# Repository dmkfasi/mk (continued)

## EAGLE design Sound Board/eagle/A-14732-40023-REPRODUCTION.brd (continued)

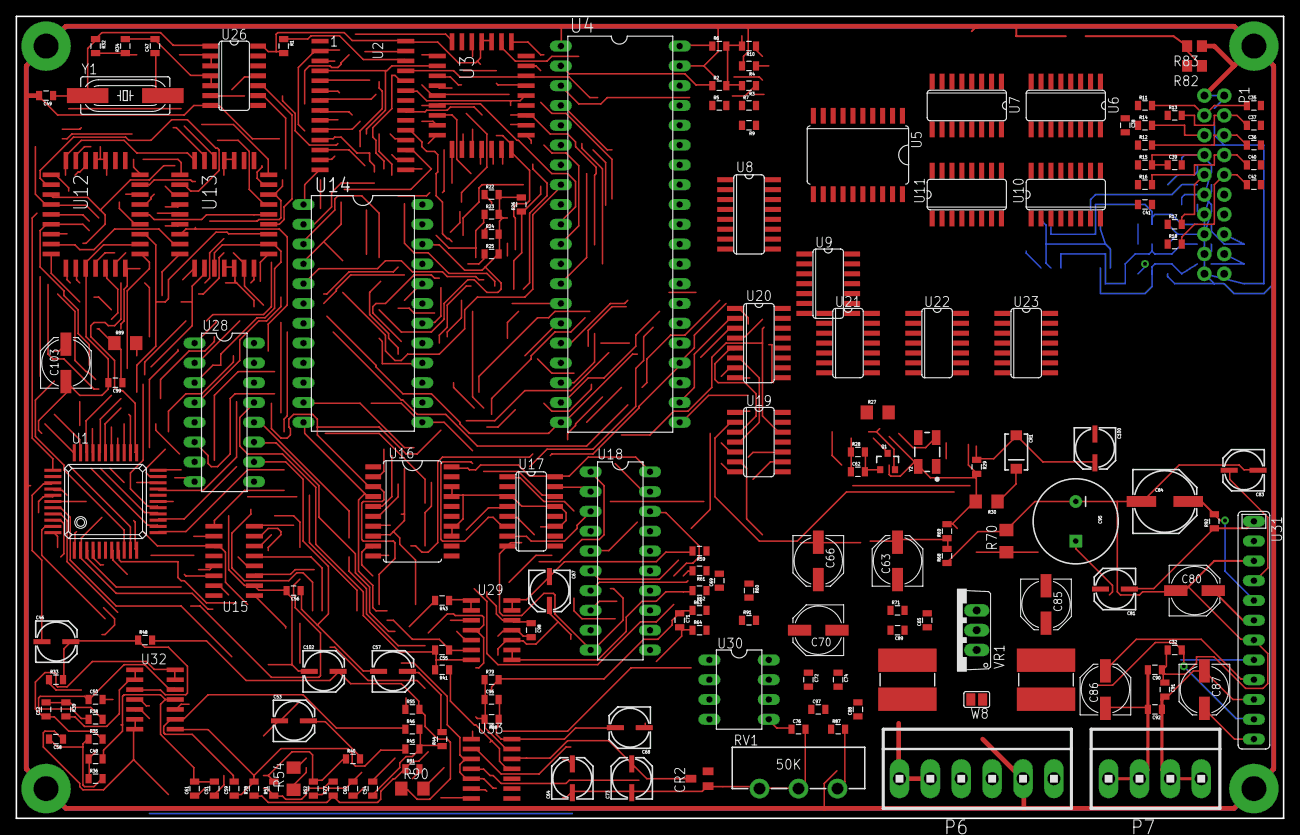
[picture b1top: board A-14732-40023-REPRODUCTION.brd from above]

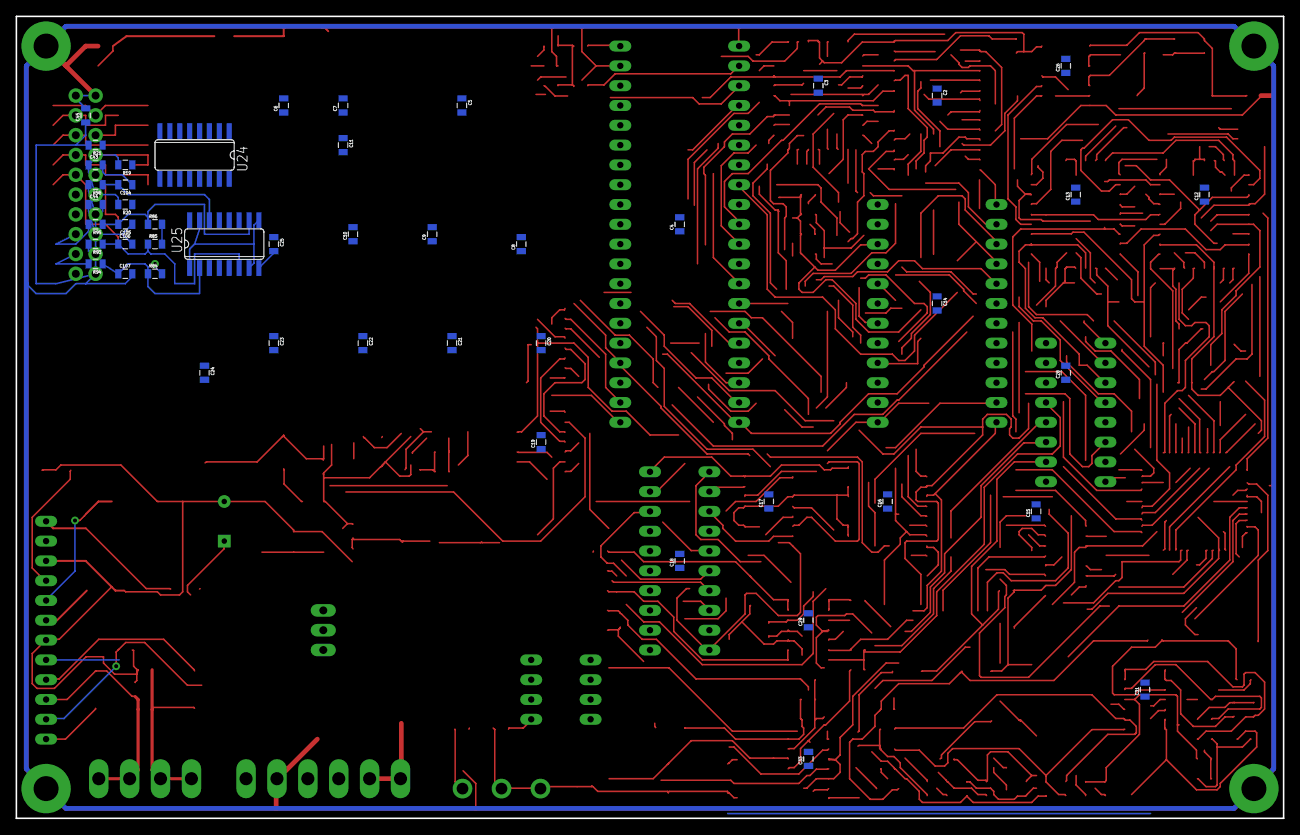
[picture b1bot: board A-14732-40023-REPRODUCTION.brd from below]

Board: 2 copper layers, 162.6 x 102.9 mm, 220 parts (48 on the bottom side), 220 nets.

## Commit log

2015-09-28 4th sheet added
2015-09-28 Removed undo files
2015-09-28 new components added
2015-09-28 fixed packages
2015-10-03 auto regenerated, nothing useful yet
2015-10-05 almost complete 4th sheet
2015-10-05 shortened 26ls31, 26ls32 to fit vertical space
2015-10-06 autogen updated
2015-10-06 P1 connected mostly wired up
2015-10-06 overwritten with new software version
2015-10-09 nothing really new
2015-10-09 completed 4th sheet, some parts name corrected
2015-10-10 regenerated
2015-10-10 26ls32 outputs dir corrected
2015-10-10 fixed YAM-OUT2 net connection, fixed mixed up GND<->AGND, fixed missed power supply pins for U5
2015-10-10 approved non-critical warnings for power supply pins
2015-10-10 approved non-critical power pins warnings
2015-10-10 first revision for 40023 assembly and T-Unit CPU board
2015-10-10 1N5232 SOT-23 package added
2015-10-10 R65 replaced with CR2 according to the official schematics
2015-10-10 1N5232 MiniMELF package added
2015-10-10 updated values, names, fixed some parts, added C104-C107 and R94-R96
2015-10-10 current version
2015-10-11 small fixes, WIP
2015-10-11 added polarized capacitors for PANASONIC_C package
2015-10-11 replaced all non-power rail resistors to 0805 size 1/8W
2015-10-11 replaced filter capacitors to 0805 size
2015-10-11 current project
2015-10-11 replaced all the polarized capacitors with PANASONIC_? package, fixed bugs, replaced C95 with a hole-through
2015-10-11 Rework of the original board with more or less modern component base
2015-10-11 fixes
2015-10-11 initial layout after autogeneration
2015-10-11 SOP28 package added for 6264 SRAM chip
2015-10-11 added PLCC32 package and socket for ROM chips
2015-10-11 corrected library for SRAM and ROM chips
2015-10-11 updated other ICs with current library in use
2015-10-11 C79 corrected to C84
2015-10-11 layout WIP
2015-10-12 corrected C30 to C59
2015-10-12 Trying to lay around, resulting in fixing misplaced components and other fixes
2015-10-18 board layout wip
2015-10-26 no need for these
2015-11-01 Moving from EAGLE to KiCad, sorting out files
2015-11-01 moving eagle files
2015-11-01 Initial KiCad project files
2015-11-01 updated components description
2015-11-01 current files
2015-11-01 moved to hierarchy sheets, added sheet #2
2015-11-03 hierarchically sheets added
2015-11-03 another attempt, still hopeless
2015-11-03 some fixes
2015-11-04 74LS174 added, other components fixes
2015-11-04 current settings
2015-11-04 fixes to MTGHOLE added size
2015-11-04 work in progress, U1, U12, U13 added
2015-11-08 OpAmp added, TIL7524 added
2015-11-08 finished
2015-11-08 re-annoted components due to moving the sheet
2015-11-08 re-annoted components due to errors
2015-11-08 some DRC errors fixed
2015-11-08 power pins corrected, bi-dir pins corrected
2015-11-08 critical DRC errors fixes
2015-11-08 sheet 3 added, power rails added to fix current ERC errors
2015-11-08 sheet 4 yet is blank
2015-11-08 added 0.156" header, midified power supply pins
2015-11-08 sheet 3 and sheet 4 added
2015-11-08 power related ERC error fixes
2015-11-11 4-6 pin connector added
2015-11-11 minor fixes
2015-11-11 work in progress, started mc3340 wiring
2015-11-15 minor fixes for labels alignment
2015-11-15 work in progress around U30/U31
2015-11-15 global labels added as initial work in progress
2015-11-21 i/o buffers size compacted to fit paper frame
2015-11-21 work in progress due to changes in library
2015-11-21 work in progress on i/o buffers connections and placement
2015-11-22 Initial drawning for control panel based on dimensions references by Twistedsymphony and Jakobud.com
2015-11-23 updated with support, top glass cover and rounded side panels
2015-11-25 reference photographs
2015-11-25 completed back side support and fixed width for metric system
2015-11-30 74LS74A added to fit sheet4
2015-11-30 work in progress, wiring i/o buffers, trying to fit everything in place
2015-12-04 Work in progress
2015-12-04 Test assembly
2015-12-04 MK2 and later version
2015-12-04 Body side panels
2015-12-04 cleaned up a little
2015-12-20 more work in progress, P1 parallel interface added, SND_DAT signals connected
2015-12-26 revert sizes back for 26LS31 and 26LS32 due to paper size of Sheet4
2015-12-26 changed properies for sheet4 title
2015-12-26 updated with last date
2015-12-26 corrected c104-c107, connected U10 INs
2015-12-26 finished with OpAMP U31
2015-12-26 finished, revised
2015-12-26 fiddle some stuff around for the best fit
2015-12-26 corrected P7 speaker out
2015-12-26 cleaned up
2015-12-26 A0 global label for Yamaha CPU added
2015-12-26 A0 global label connected to CPU address bus
2015-12-26 OpAMP positive feedback input pulled up 12V with Zener diode
2016-01-12 updated footprints, work in progress
2016-01-15 oscillator rework for DIL8 package
2016-01-15 current library
2016-01-15 updating footprints
2016-01-24 Open Hardware License
2016-01-24 Revision 2 schematic
2016-01-24 Revision 1 board layout
2016-01-24 Current netlist
2016-01-24 Revision 2
2016-01-24 Revision 2 cleaned up
2016-01-24 Fabrication files
2016-02-06 Updated footprints
2016-02-06 New euroboard layout 160x100mm with rounded corners and mounting holes
2016-02-12 New layout for larger board of 180x120mm
2016-02-12 now using pin header as package for U31 to display more or less properly in a 3D view
2016-02-12 current layout for 180x120mm size
2016-02-12 changed package for U31 to pin header for proper display in 3D PCB view
2016-02-14 All components placed, time to play around
2016-02-14 fiddling around
2016-02-18 playing-laying
2016-02-19 playing around
2016-03-08 Upgraded to FreeCAD 0.16, mounting axis A4 template created for actual application
2016-03-08 Printable template for drilling button holes
2016-03-27 Moved ruler to User.drwg, slightly narrowed board for better sit of P1 control panel connector and moved its name to a place where it is going to be visible after soldering angled pin header
2016-03-27 new production files for fixed PCB
2017-01-17 Update README.md
    typos
2017-01-23 New layout
2017-01-23 New netlist
2017-01-23 Redraw with SOT-23 diodes for MK4 RUN buttons
2017-01-23 Complete Rev.2.1
2017-01-23 Revision 2.1 gerber file
2017-01-23 PCB render image
2017-01-24 New mount drill positions
2017-01-24 New mount hole positions
2017-01-24 Updated look, red coating
